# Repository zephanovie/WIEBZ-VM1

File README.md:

# WIEBZ-VM1
# THIS PROJECT IS INCOMPLETE !!!!!

here are some design pics for now or you can check the current progress in the journal

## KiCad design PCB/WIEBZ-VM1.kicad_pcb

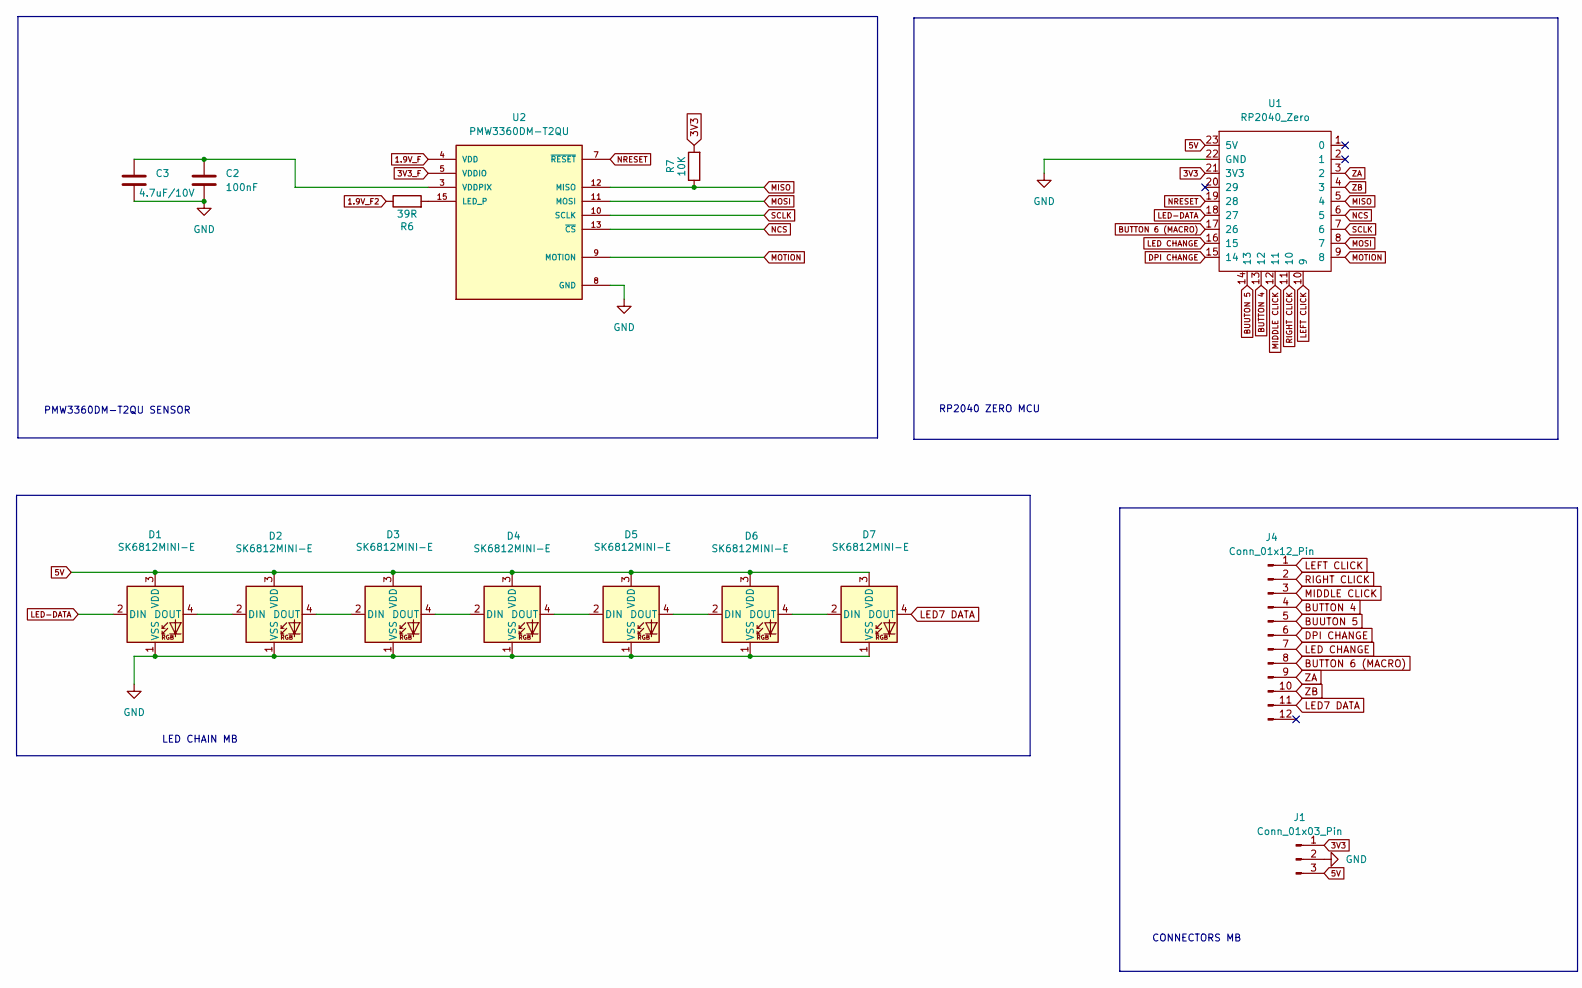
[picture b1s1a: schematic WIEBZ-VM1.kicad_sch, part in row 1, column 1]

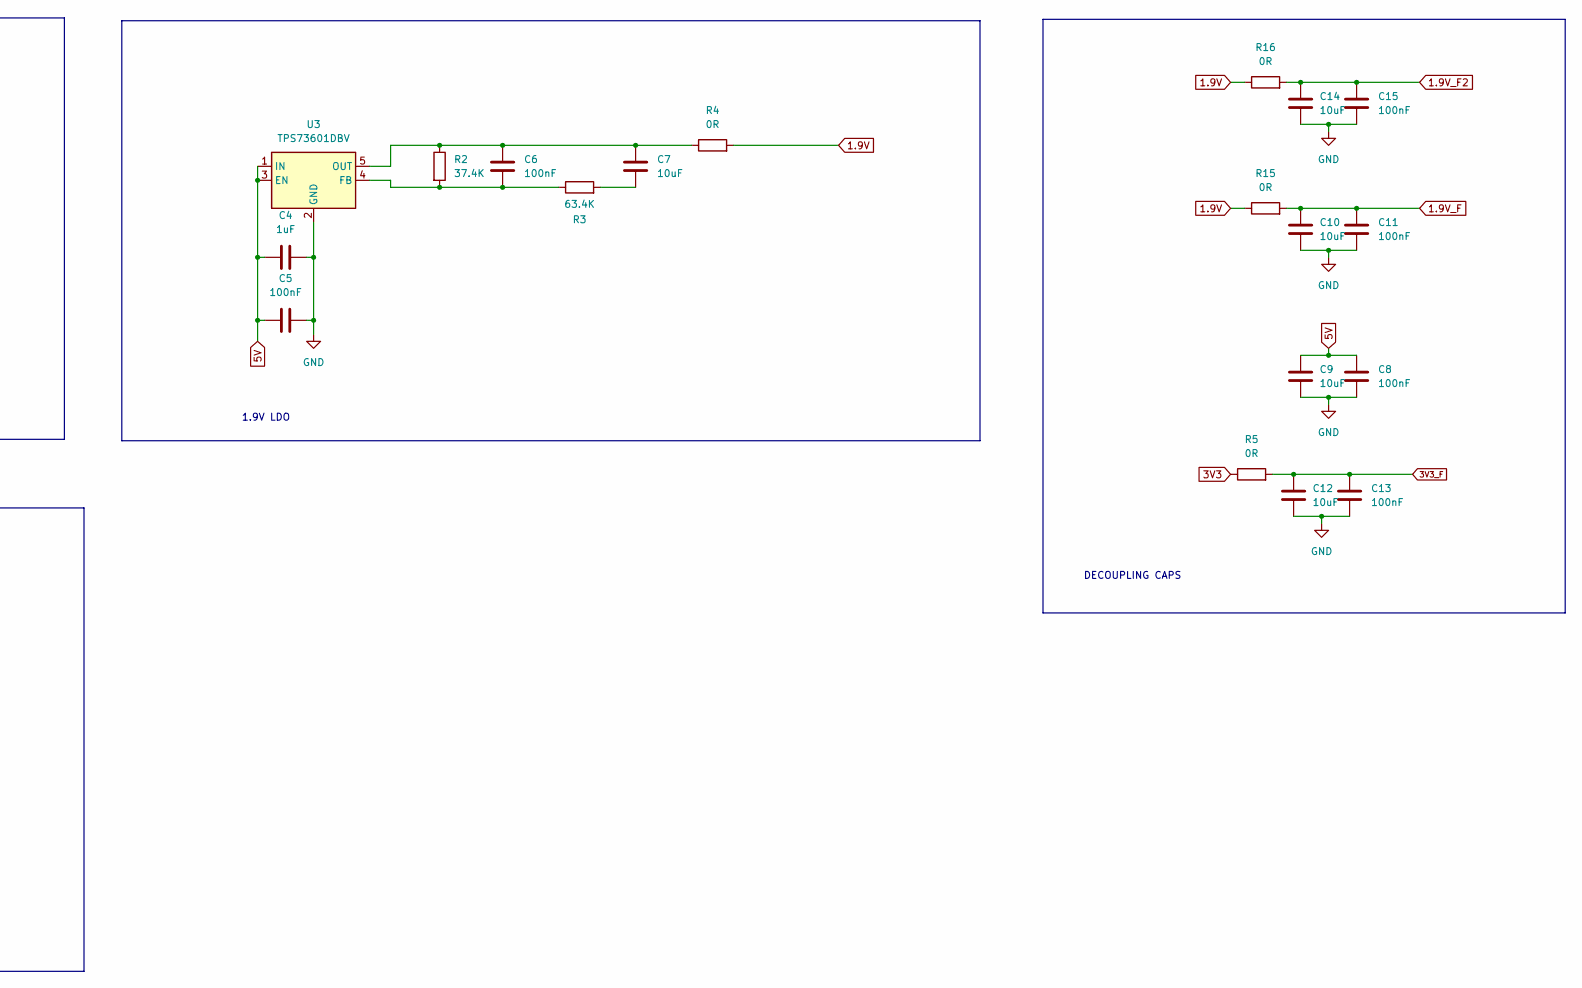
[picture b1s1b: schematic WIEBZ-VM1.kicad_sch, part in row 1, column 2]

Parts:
C2, C5, C6, C8, C11, C13, C15: 100nF; Resistor_1206
C3: 4.7uF/10V; Resistor_1206
C4: 1uF; Resistor_1206
C7, C9, C10, C12, C14: 10uF; Resistor_1206
D1, D2, D3, D4, D5, D6, D7: SK6812MINI-E; LED_SK6812MINI-E_3.2x2.8mm_P1.5mm_ReverseMount
J1: Conn_01x03_Pin; JST_ZH_B3B-ZR_1x03_P1.50mm_Vertical
J4: Conn_01x12_Pin; JST_ZH_B12B-ZR_1x12_P1.50mm_Vertical
R2: 37.4K; Resistor_1206
R3: 63.4K; Resistor_1206
R4, R5, R15, R16: 0R; Resistor_1206
R6: 39R; Resistor_1206
R7: 10K; Resistor_1206
U1: RP2040_Zero
U2: PMW3360DM-T2QU; PMW3360; MANUFACTURER_PART_NUMBER PMW3360DM-T2QU
U3: TPS73601DBV; SOT-23-5

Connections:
1.9V: R4.2, R15.1, R16.1
1.9V_F: C10.1, C11.1, R15.2, U2.4 (VDD)
1.9V_F2: C14.1, C15.1, R6.1, R16.2
3V3: J1.1, R5.1, R7.2, U1.21 (3V3)
3V3_F: C12.1, C13.1, R5.2, U2.5 (VDDIO)
5V: C4.1, C5.1, C8.1, C9.1, D1.3 (VDD), D2.3 (VDD), D3.3 (VDD), D4.3 (VDD), D5.3 (VDD), D6.3 (VDD), D7.3 (VDD), J1.3, U1.23 (5V), U3.1 (IN), U3.3 (EN)
BUTTON 4: J4.4, U1.13 (12)
BUTTON 6 (MACRO): J4.8, U1.17 (26)
BUUTON 5: J4.5, U1.14 (13)
DPI CHANGE: J4.6, U1.15 (14)
GND: C2.2, C3.2, C4.2, C5.2, C8.2, C9.2, C10.2, C11.2, C12.2, C13.2, C14.2, C15.2, D1.1 (VSS), D2.1 (VSS), D3.1 (VSS), D4.1 (VSS), D5.1 (VSS), D6.1 (VSS), D7.1 (VSS), J1.2, U1.22 (GND), U2.8 (GND), U3.2 (GND)
LED7 DATA: D7.4 (DOUT), J4.11
LED CHANGE: J4.7, U1.16 (15)
LED-DATA: D1.2 (DIN), U1.18 (27)
LEFT CLICK: J4.1, U1.10 (9)
MIDDLE CLICK: J4.3, U1.12 (11)
MISO: R7.1, U1.5 (4), U2.12 (MISO)
MOSI: U1.8 (7), U2.11 (MOSI)
MOTION: U1.9 (8), U2.9 (MOTION)
NCS: U1.6 (5), U2.13 (~CS)
NRESET: U1.19 (28), U2.7 (~RESET)
unnamed: C7.2, R3.2
unnamed: D1.4 (DOUT), D2.2 (DIN)
unnamed: D2.4 (DOUT), D3.2 (DIN)
unnamed: D3.4 (DOUT), D4.2 (DIN)
unnamed: D4.4 (DOUT), D5.2 (DIN)
unnamed: D5.4 (DOUT), D6.2 (DIN)
unnamed: D6.4 (DOUT), D7.2 (DIN)
unnamed: R6.2, U2.15 (LED_P)
unnamed: C2.1, C3.1, U2.3 (VDDPIX)
unnamed: C6.2, R2.2, R3.1, U3.4 (FB)
unnamed: C6.1, C7.1, R2.1, R4.1, U3.5 (OUT)
RIGHT CLICK: J4.2, U1.11 (10)
SCLK: U1.7 (6), U2.10 (SCLK)
ZA: J4.9, U1.3 (2)
ZB: J4.10, U1.4 (3)

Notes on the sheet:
LED CHAIN MB
PMW3360DM-T2QU SENSOR
RP2040 ZERO MCU
CONNECTORS MB
1.9V LDO
DECOUPLING CAPS

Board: 2 copper layers, 34 parts (0 on the bottom side), 36 nets, no tracks yet.

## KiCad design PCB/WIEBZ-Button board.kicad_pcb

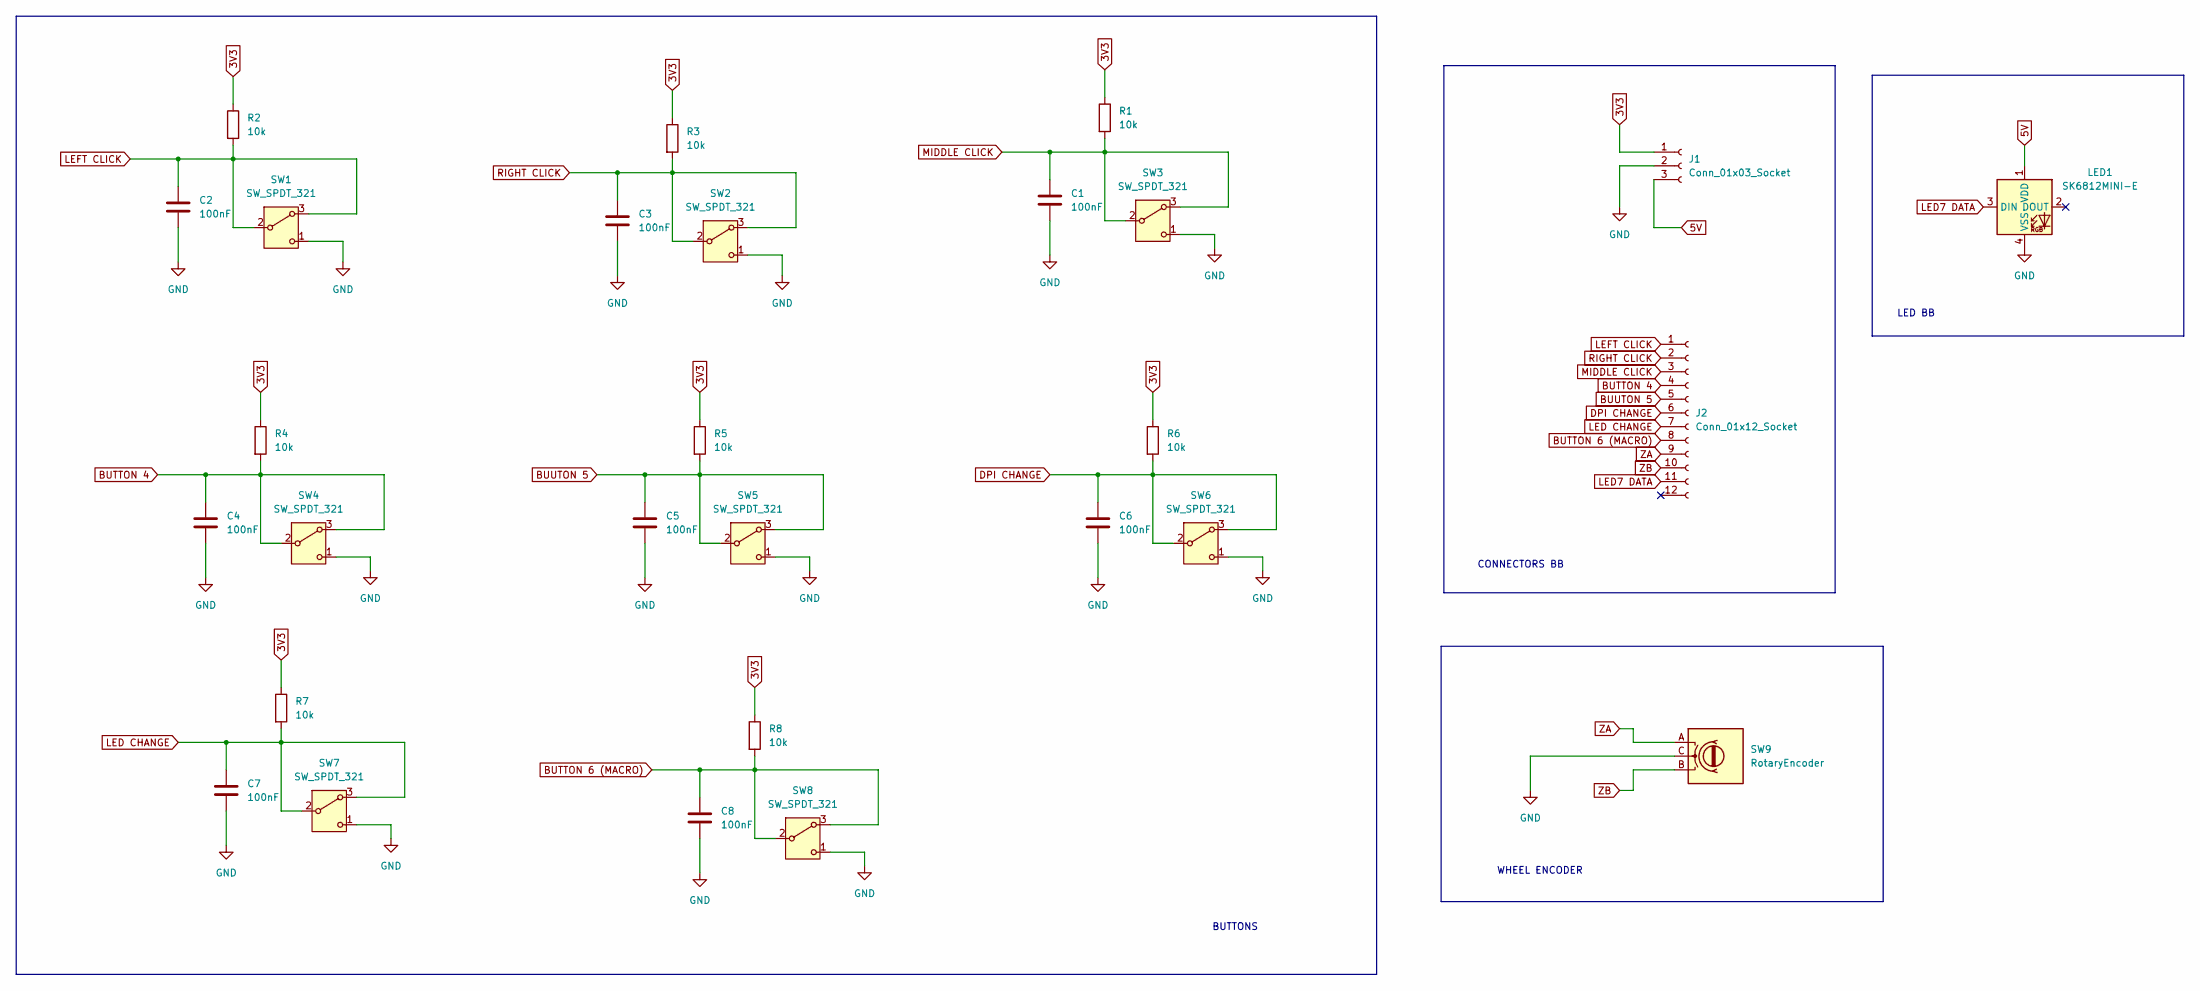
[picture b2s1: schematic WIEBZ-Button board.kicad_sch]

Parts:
C1, C2, C3, C4, C5, C6, C7, C8: 100nF; C_1206_3216Metric_Pad1.33x1.80mm_HandSolder
J1: Conn_01x03_Socket; JST_ZH_B3B-ZR_1x03_P1.50mm_Vertical
J2: Conn_01x12_Socket; JST_ZH_B12B-ZR_1x12_P1.50mm_Vertical
LED1: SK6812MINI-E; LED_6028R
R1, R2, R3, R4, R5, R6, R7, R8: 10k; R_1206_3216Metric_Pad1.30x1.75mm_HandSolder
SW1, SW2, SW3, SW4, SW5, SW6, SW7, SW8: SW_SPDT_321; SW_D2FC-F-7N_100M_
SW9: RotaryEncoder; Kailh Wheel Encoder

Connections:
3V3: J1.1, R1.1, R2.1, R3.1, R4.1, R5.1, R6.1, R7.1, R8.1
5V: J1.3, LED1.1 (VDD)
BUTTON 4: C4.1, J2.4, R4.2, SW4.2 (B), SW4.3 (A)
BUTTON 6 (MACRO): C8.1, J2.8, R8.2, SW8.2 (B), SW8.3 (A)
BUUTON 5: C5.1, J2.5, R5.2, SW5.2 (B), SW5.3 (A)
DPI CHANGE: C6.1, J2.6, R6.2, SW6.2 (B), SW6.3 (A)
GND: C1.2, C2.2, C3.2, C4.2, C5.2, C6.2, C7.2, C8.2, J1.2, LED1.4 (VSS), SW1.1 (C), SW2.1 (C), SW3.1 (C), SW4.1 (C), SW5.1 (C), SW6.1 (C), SW7.1 (C), SW8.1 (C), SW9.C
LED7 DATA: J2.11, LED1.3 (DIN)
LED CHANGE: C7.1, J2.7, R7.2, SW7.2 (B), SW7.3 (A)
LEFT CLICK: C2.1, J2.1, R2.2, SW1.2 (B), SW1.3 (A)
MIDDLE CLICK: C1.1, J2.3, R1.2, SW3.2 (B), SW3.3 (A)
RIGHT CLICK: C3.1, J2.2, R3.2, SW2.2 (B), SW2.3 (A)
ZA: J2.9, SW9.A
ZB: J2.10, SW9.B

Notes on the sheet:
WHEEL ENCODER
LED BB
BUTTONS
CONNECTORS BB

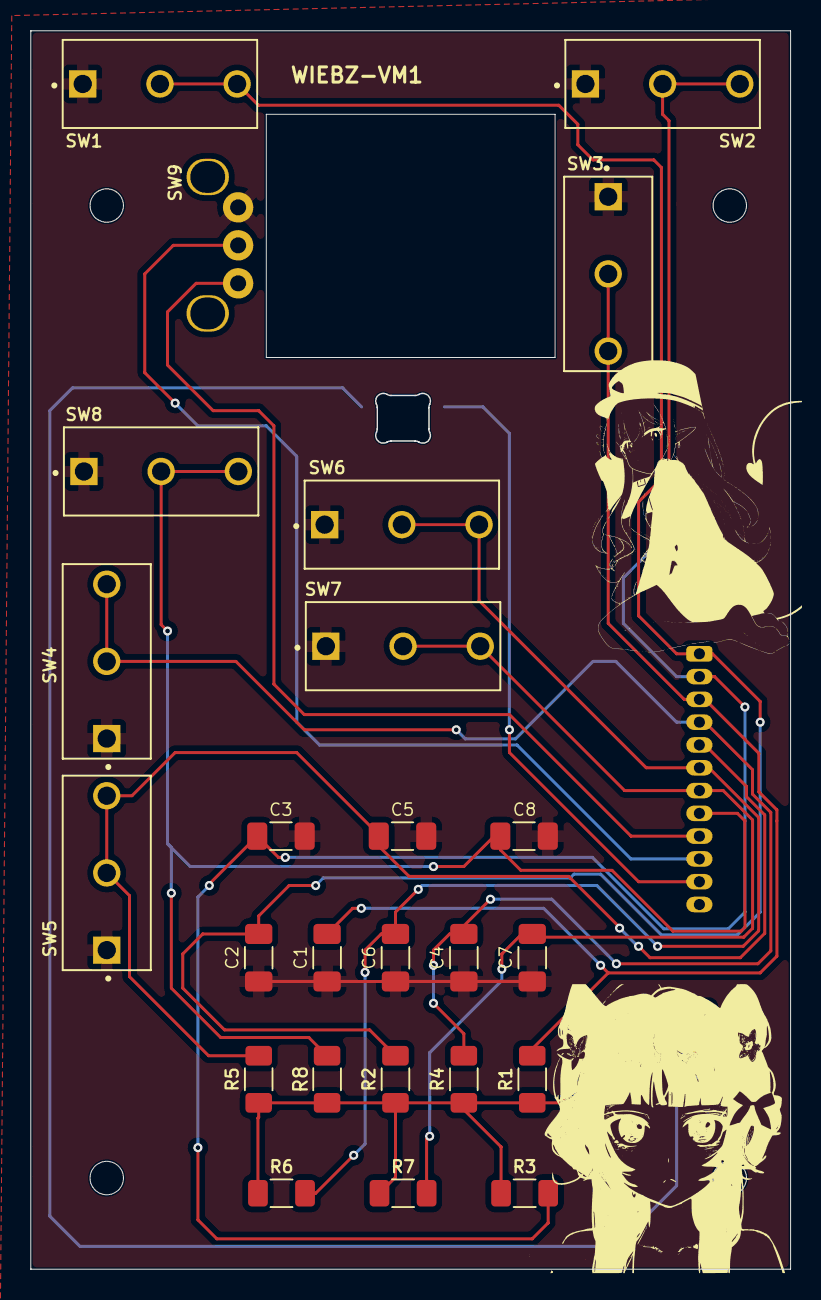
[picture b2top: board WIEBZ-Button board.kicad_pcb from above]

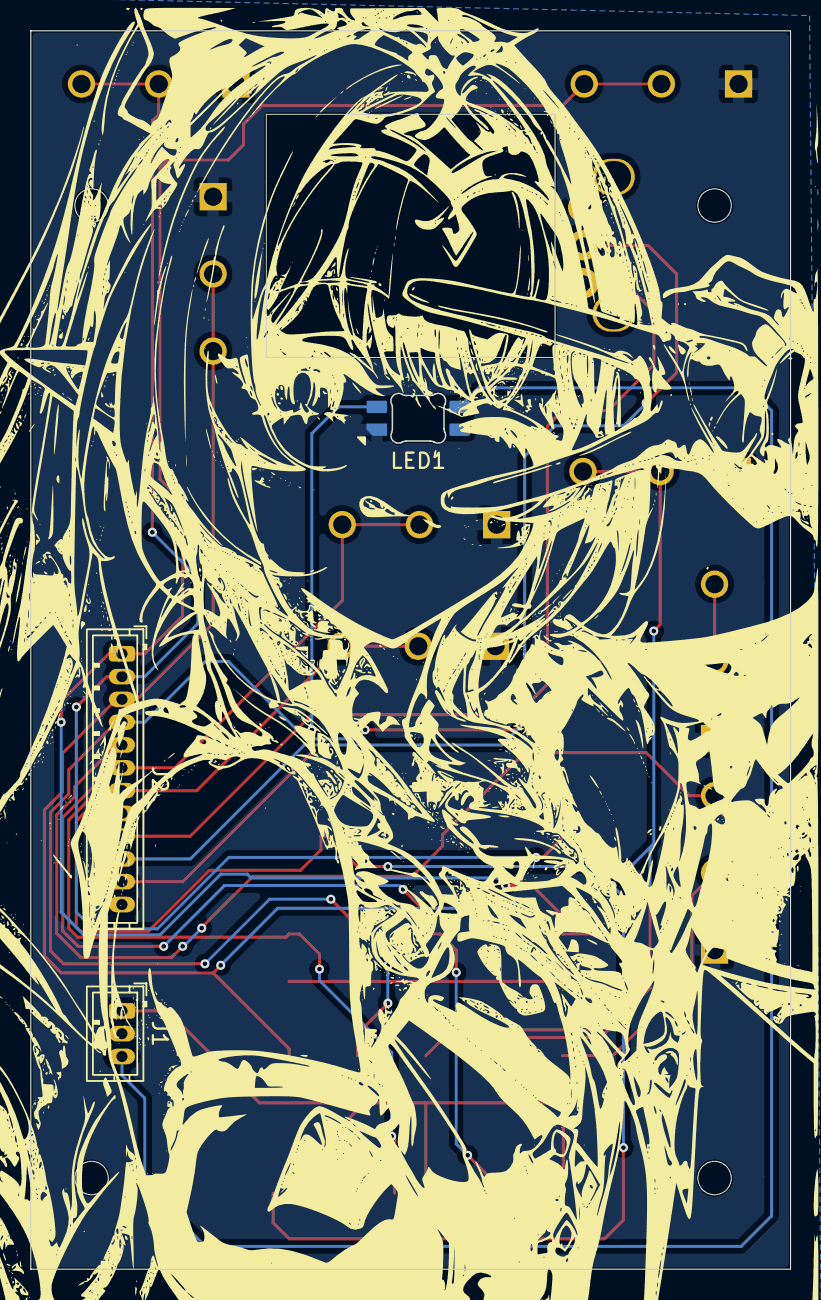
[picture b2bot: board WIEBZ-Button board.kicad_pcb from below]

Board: 2 copper layers, 50.0 x 81.5 mm, 28 parts (3 on the bottom side), 14 nets.
